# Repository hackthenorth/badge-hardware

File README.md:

# badge-hardware
Physical Hardware Designs for the 2026 Hacker Badge Project

IBOM Link: https://hackathon.github.io/badge-hardware/badge-ibom.html

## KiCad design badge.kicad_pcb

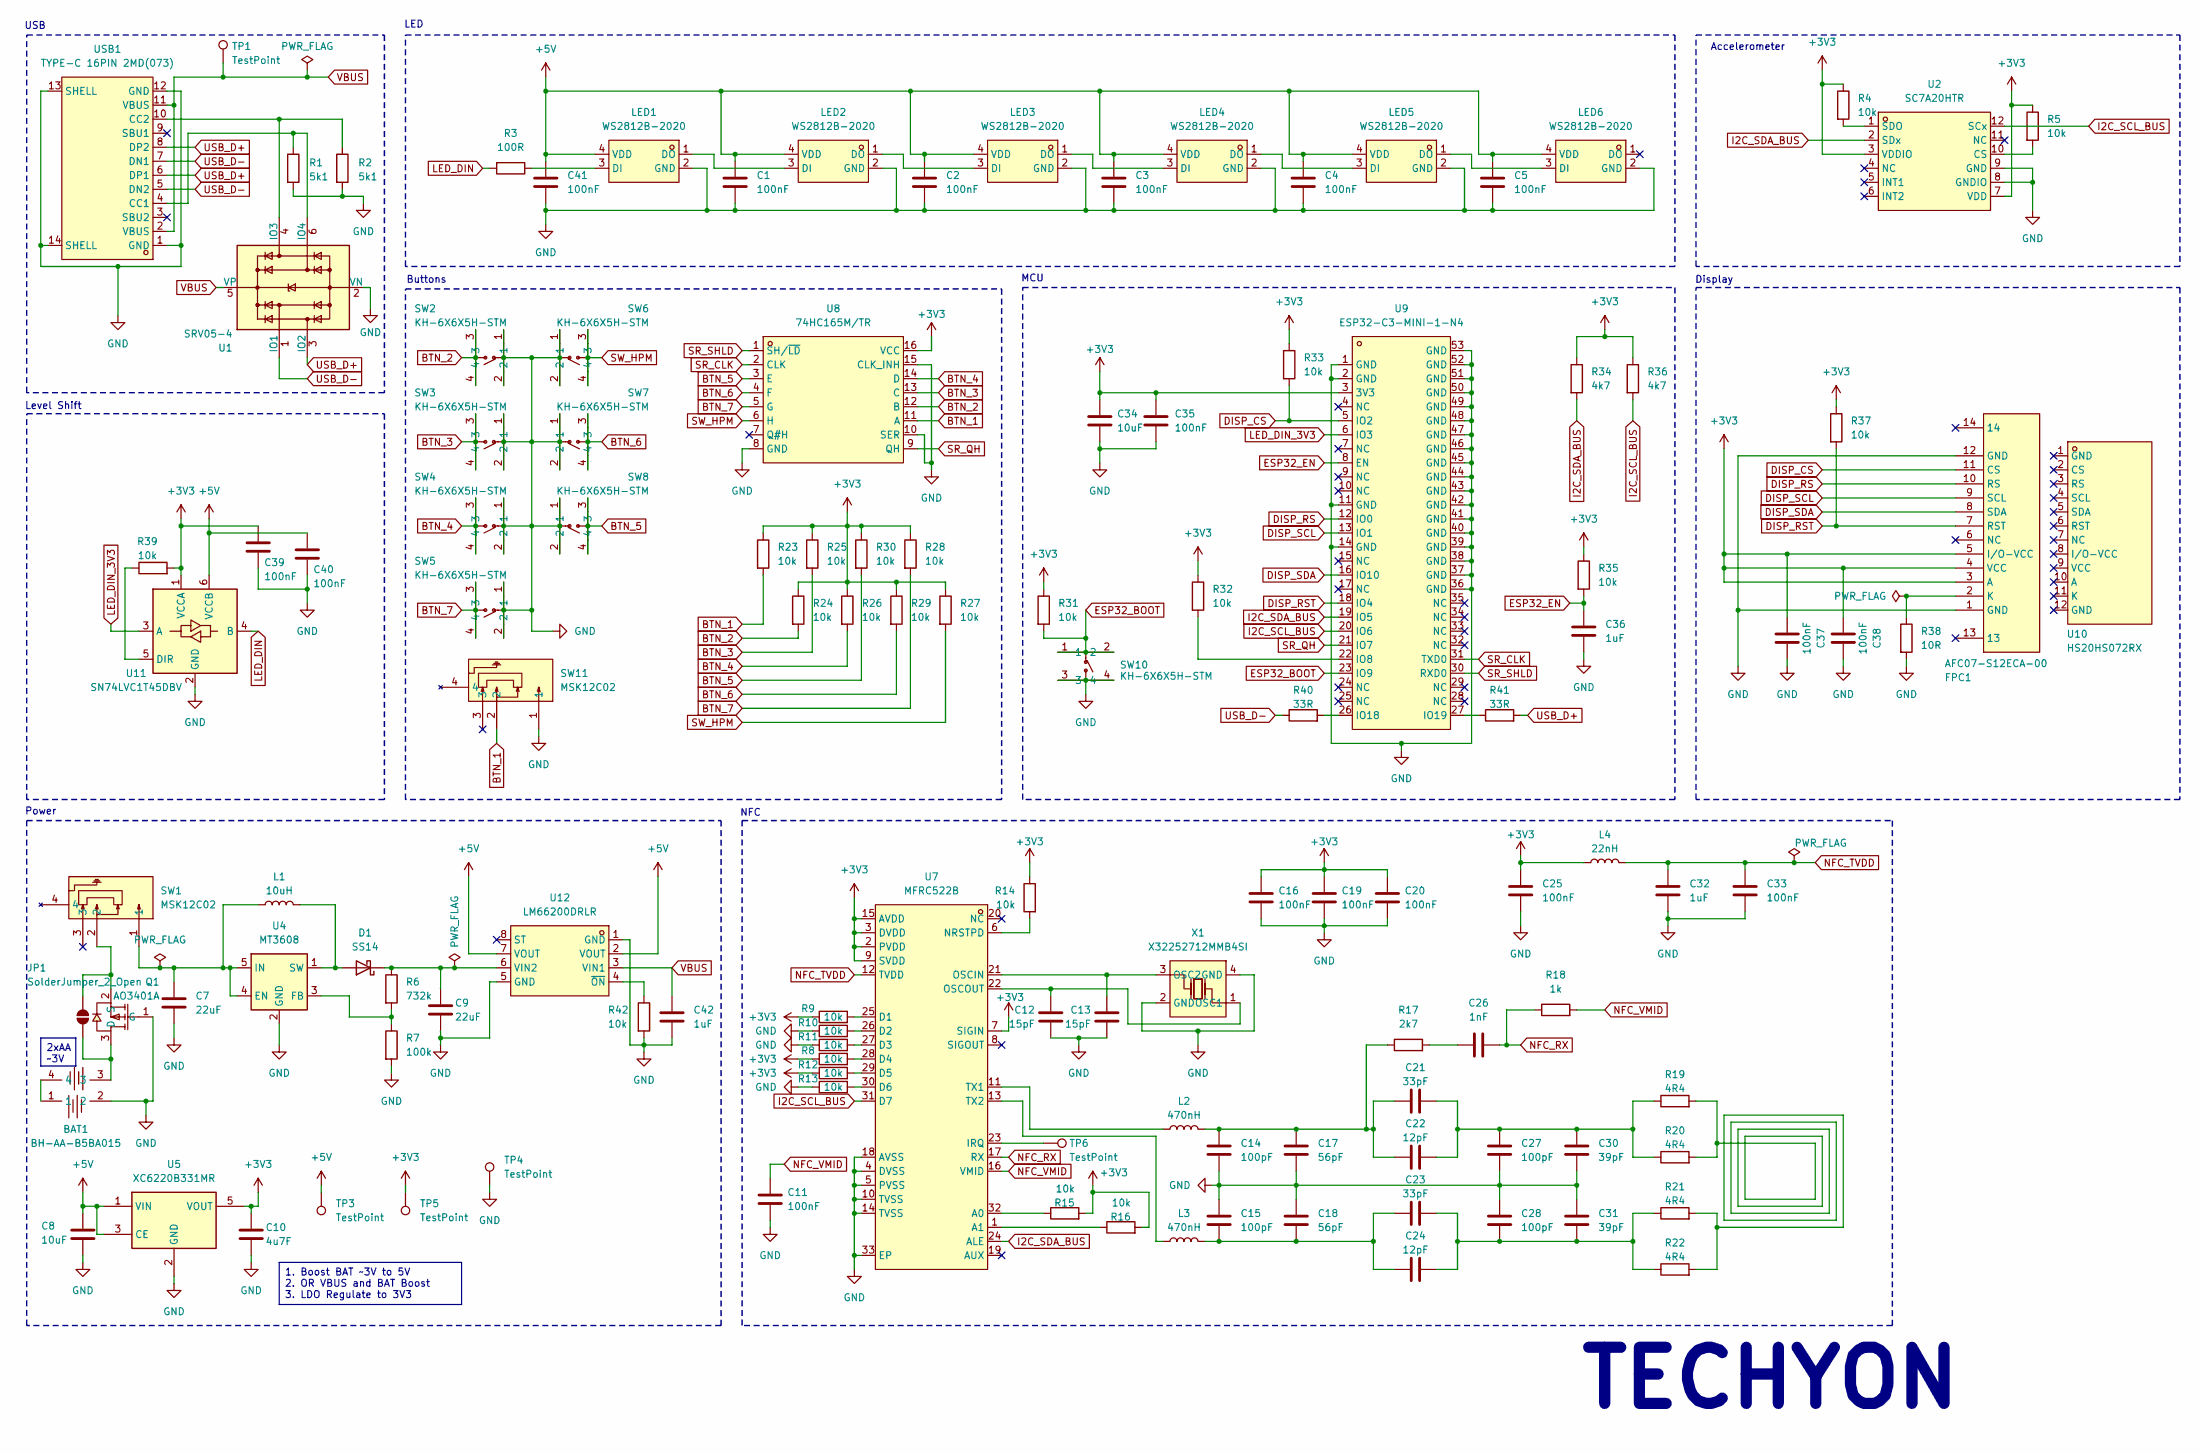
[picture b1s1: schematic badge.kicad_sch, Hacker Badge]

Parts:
BAT1: BH-AA-B5BA015; BAT-SMD_BH-AA-B5BA015; LCSC Part C5290182
C1, C2, C3, C4, C5, C11, C16, C19, C20, C25, C33, C41: 100nF; C_0805_2012Metric
C7, C9: 22uF; C_0805_2012Metric; LCSC Part C45783
C8, C34: 10uF; C_0805_2012Metric; LCSC Part C440198
C10: 4u7F; C_0805_2012Metric; LCSC Part C1779
C12, C13: 15pF; C_0805_2012Metric
C14, C15, C27, C28: 100pF; C_0805_2012Metric
C17, C18: 56pF; C_0805_2012Metric
C21, C23: 33pF; C_0805_2012Metric
C22, C24: 12pF; C_0805_2012Metric
C26: 1nF; C_0805_2012Metric
C30, C31: 39pF; C_0805_2012Metric
C32, C42: 1uF; C_0805_2012Metric
C35, C37, C38, C39, C40: 100nF; C_0805_2012Metric; LCSC Part C49678
C36: 1uF; C_0805_2012Metric; LCSC Part C28323
D1: SS14; D_SMA; LCSC Part C2480
FPC1: AFC07-S12ECA-00; FPC-SMD_12P-P0.50_AFC07-S12ECA-00; LCSC Part C262585
JP1: SolderJumper_2_Open; SolderJumper-2_P1.3mm_Open_Pad1.0x1.5mm
L1: 10uH; L_0805_2012Metric; LCSC Part C440198
L2, L3: 470nH; L_0805_2012Metric
L4: 22nH; L_0805_2012Metric
LED1, LED2, LED3, LED4, LED5, LED6: WS2812B-2020; LED-SMD_4P-L2.0-W2.0-TL_WS2812B-2020; LCSC Part C965555
Q1: AO3401A; SOT-23_L2.9-W1.3-P1.90-LS2.4-BR; MPN AO3401A; LCSC Part C15127
R1, R2: 5k1; R_0805_2012Metric; LCSC Part C27834
R3: 100R; R_0805_2012Metric
R4, R5, R8, R9, R10, R11, R12, R13, R14, R15, R16, R23, R24, R25, R26, R27, R28, R29, R30, R32, R33, R42: 10k; R_0805_2012Metric
R6: 732k; R_0805_2012Metric; LCSC Part C2684593
R7: 100k; R_0805_2012Metric; LCSC Part C149504
R17: 2k7; R_0805_2012Metric
R18: 1k; R_0805_2012Metric
R19, R20, R21, R22: 4R4; R_0805_2012Metric
R31, R35, R37, R39: 10k; R_0805_2012Metric; LCSC Part C17414
R34, R36: 4k7; R_0805_2012Metric
R38: 10R; R_0805_2012Metric; LCSC Part C17415
R40, R41: 33R; R_0805_2012Metric
SW1, SW11: MSK12C02; SW-TH_MSK12C02; LCSC Part C431540
SW2, SW3, SW4, SW5, SW6, SW7, SW8, SW10: KH-6X6X5H-STM; SW-SMD_4P-L6.0-W6.0-P4.50-LS9.0_H5.0; LCSC Part C2837531
TP1, TP3, TP4, TP5, TP6: TestPoint; TestPoint_Pad_D1.5mm
U1: SRV05-4; SOT-23-6; LCSC Part C7420376
U2: SC7A20HTR; LGA-12_L2.0-W2.0-P0.50-TL; LCSC Part C19274408
U4: MT3608; SOT-23-6; LCSC Part C84817
U5: XC6220B331MR; SOT-23-5; LCSC Part C22466451
U7: MFRC522B; VQFN-32_L5.0-W5.0-P0.50-BL-EP3.3; LCSC Part C41361613
U8: 74HC165M/TR; SOP-16_L10.0-W3.9-P1.27-LS6.0-BL; LCSC Part C507184
U9: ESP32-C3-MINI-1-N4; WIFIM-SMD_ESP32-C3-MINI-1; LCSC Part C2838502
U10: HS20HS072RX; OLED-SMD_HS20HS072RX; LCSC Part C5329582
U11: SN74LVC1T45DBV; SOT-23-6; LCSC Part C7843
U12: LM66200DRLR; SOT-583-8_L2.1-W1.2-P0.50-LS1.6-BL; LCSC Part C3235556
USB1: TYPE-C 16PIN 2MD(073); USB-C-SMD_TYPE-C-6PIN-2MD-073; LCSC Part C2765186
X1: X32252712MMB4SI; CRYSTAL-SMD_4P-L3.2-W2.5-BL-1; LCSC Part C29975

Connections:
+3V3: C10.2, C16.1, C19.1, C20.1, C25.1, C34.1, C35.1, C37.2, C38.2, C39.1, FPC1.3 (A), FPC1.4 (VCC), FPC1.5 (I/O-VCC), L4.1, R4.1, R5.1, R8.1, R9.1, R12.1, R14.1, R15.2, R16.2, R23.1, R24.1, R25.1, R26.1, R27.1, R28.1, R29.1, R30.1, R31.1, R32.1, R33.1, R34.1, R35.1, R36.1, R37.1, R39.2, TP5.1, U2.3 (VDDIO), U2.7 (VDD), U5.5 (VOUT), U7.2 (PVDD), U7.3 (DVDD), U7.7 (SIGIN), U7.9 (SVDD), U7.15 (AVDD), U8.16 (VCC), U9.3 (3V3), U11.1 (VCCA)
+5V: C1.1, C2.1, C3.1, C4.1, C5.1, C8.2, C40.1, C41.1, LED1.4 (VDD), LED2.4 (VDD), LED3.4 (VDD), LED4.4 (VDD), LED5.4 (VDD), LED6.4 (VDD), TP3.1, U5.1 (VIN), U5.3 (CE), U11.6 (VCCB), U12.2 (VOUT), U12.7 (VOUT)
BTN_1: R23.2, SW11.2, U8.11 (A)
BTN_2: R24.2, SW2.3, SW2.4, U8.12 (B)
BTN_3: R25.2, SW3.3, SW3.4, U8.13 (C)
BTN_4: R26.2, SW4.3, SW4.4, U8.14 (D)
BTN_5: R30.2, SW8.3, SW8.4, U8.3 (E)
BTN_6: R29.2, SW7.3, SW7.4, U8.4 (F)
BTN_7: R28.2, SW5.3, SW5.4, U8.5 (G)
DISP_CS: FPC1.11 (CS), R33.2, U9.5 (IO2)
DISP_RS: FPC1.10 (RS), U9.12 (IO0)
DISP_RST: FPC1.7 (RST), R37.2, U9.18 (IO4)
DISP_SCL: FPC1.9 (SCL), U9.13 (IO1)
DISP_SDA: FPC1.8 (SDA), U9.16 (IO10)
ESP32_BOOT: R31.2, SW10.1, SW10.2, U9.23 (IO9)
ESP32_EN: C36.1, R35.2, U9.8 (EN)
GND: BAT1.2, C1.2, C2.2, C3.2, C4.2, C5.2, C7.2, C8.1, C9.2, C10.1, C11.2, C12.2, C13.2, C14.2, C15.1, C16.2, C17.2, C18.1, C19.2, C20.2, C25.2, C27.2, C28.1, C30.2, C31.1, C32.2, C33.2, C34.2, C35.2, C36.2, C37.1, C38.1, C39.2, C40.2, C41.2, C42.2, FPC1.1 (GND), FPC1.12 (GND), LED1.2 (GND), LED2.2 (GND), LED3.2 (GND), LED4.2 (GND), LED5.2 (GND), LED6.2 (GND), Q1.1 (G), R1.2, R2.2, R7.2, R10.1, R11.1, R13.1, R38.2, R42.2, SW2.1, SW2.2, SW3.1, SW3.2, SW4.1, SW4.2, SW5.1, SW5.2, SW6.1, SW6.2, SW7.1, SW7.2, SW8.1, SW8.2, SW10.3, SW10.4, SW11.1, TP4.1, U1.2 (VN), U2.8 (GNDIO), U2.9 (GND), U4.2 (GND), U5.2 (GND), U7.4 (DVSS), U7.5 (PVSS), U7.10 (TVSS), U7.14 (TVSS), U7.18 (AVSS), U7.33 (EP), U8.8 (GND), U8.10 (SER), U8.15 (CLK_INH), U9.1 (GND), U9.2 (GND), U9.11 (GND), U9.14 (GND), U9.36 (GND), U9.37 (GND), U9.38 (GND), U9.39 (GND), U9.40 (GND), U9.41 (GND), U9.42 (GND), U9.43 (GND), U9.44 (GND), U9.45 (GND), U9.46 (GND), U9.47 (GND), U9.48 (GND), U9.49 (GND), U9.50 (GND), U9.51 (GND), U9.52 (GND), U9.53 (GND), U11.2 (GND), U12.1 (GND), U12.5 (GND), USB1.1 (GND), USB1.12 (GND), USB1.13 (SHELL), USB1.14 (SHELL), X1.2 (GND), X1.4 (GND)
I2C_SCL_BUS: R36.2, U2.12 (SCx), U7.31 (D7), U9.20 (IO6)
I2C_SDA_BUS: R34.2, U2.2 (SDx), U7.24 (ALE), U9.19 (IO5)
LED_DIN: R3.2, U11.4 (B)
LED_DIN_3V3: U9.6 (IO3), U11.3 (A)
NFC_RX: C26.2, R18.1, U7.17 (RX)
NFC_TVDD: C32.1, C33.1, L4.2, U7.12 (TVDD)
NFC_VMID: C11.1, R18.2, U7.16 (VMID)
unnamed: BAT1.1, BAT1.4
unnamed: C14.1, C17.1, C21.1, C22.1, L2.2, R17.1
unnamed: C15.2, C18.2, C23.1, C24.1, L3.2
unnamed: C21.2, C22.2, C27.1, C30.1, R19.1, R20.1
unnamed: C23.2, C24.2, C28.2, C31.2, R21.1, R22.1
unnamed: C26.1, R17.2
unnamed: D1.2 (A), L1.2, U4.1 (SW)
unnamed: C9.1, D1.1 (K), R6.1, U12.6 (VIN2)
unnamed: FPC1.2 (K), R38.1
unnamed: BAT1.3, JP1.1 (A), Q1.3 (D)
unnamed: JP1.2 (B), Q1.2 (S), SW1.2
unnamed: LED1.3 (DI), R3.1
unnamed: LED1.1 (DO), LED2.3 (DI)
unnamed: LED2.1 (DO), LED3.3 (DI)
unnamed: LED3.1 (DO), LED4.3 (DI)
unnamed: LED4.1 (DO), LED5.3 (DI)
unnamed: LED5.1 (DO), LED6.3 (DI)
unnamed: R19.2, R20.2, R21.2, R22.2
unnamed: R2.1, U1.4 (IO3), USB1.10 (CC2)
unnamed: R1.1, U1.6 (IO4), USB1.4 (CC1)
unnamed: R5.2, U2.10 (CS)
unnamed: R4.2, U2.1 (SDO)
unnamed: C7.1, L1.1, SW1.1, U4.4 (EN), U4.5 (IN)
unnamed: R6.2, R7.1, U4.3 (FB)
unnamed: R15.1, U7.32 (A0)
unnamed: R16.1, U7.1 (A1)
unnamed: R9.2, U7.25 (D1)
unnamed: R10.2, U7.26 (D2)
unnamed: R11.2, U7.27 (D3)
unnamed: R8.2, U7.28 (D4)
unnamed: R12.2, U7.29 (D5)
unnamed: R13.2, U7.30 (D6)
unnamed: TP6.1, U7.23 (IRQ)
unnamed: R14.2, U7.6 (NRSTPD)
unnamed: C13.1, U7.21 (OSCIN), X1.3 (OSC2)
unnamed: C12.1, U7.22 (OSCOUT), X1.1 (OSC1)
unnamed: L2.1, U7.11 (TX1)
unnamed: L3.1, U7.13 (TX2)
unnamed: R32.2, U9.22 (IO8)
unnamed: R40.2, U9.26 (IO18)
unnamed: R41.1, U9.27 (IO19)
unnamed: R39.1, U11.5 (DIR)
unnamed: R42.1, U12.4 (~ON)
SR_CLK: U8.2 (CLK), U9.31 (TXD0)
SR_QH: U8.9 (QH), U9.21 (IO7)
SR_SHLD: U8.1 (SH/~LD), U9.30 (RXD0)
SW_HPM: R27.2, SW6.3, SW6.4, U8.6 (H)
USB_D+: R41.2, U1.3 (IO2), USB1.6 (DP1), USB1.8 (DP2)
USB_D-: R40.1, U1.1 (IO1), USB1.5 (DN2), USB1.7 (DN1)
VBUS: C42.1, TP1.1, U1.5 (VP), U12.3 (VIN1), USB1.2 (VBUS), USB1.11 (VBUS)

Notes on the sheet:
USB
Display
NFC
TECHYON
LED
Power
Buttons
Accelerometer
Level Shift
MCU
2xAA ~3V
1. Boost BAT ~3V to 5V 2. OR VBUS and BAT Boost 3. LDO Regulate to 3V3

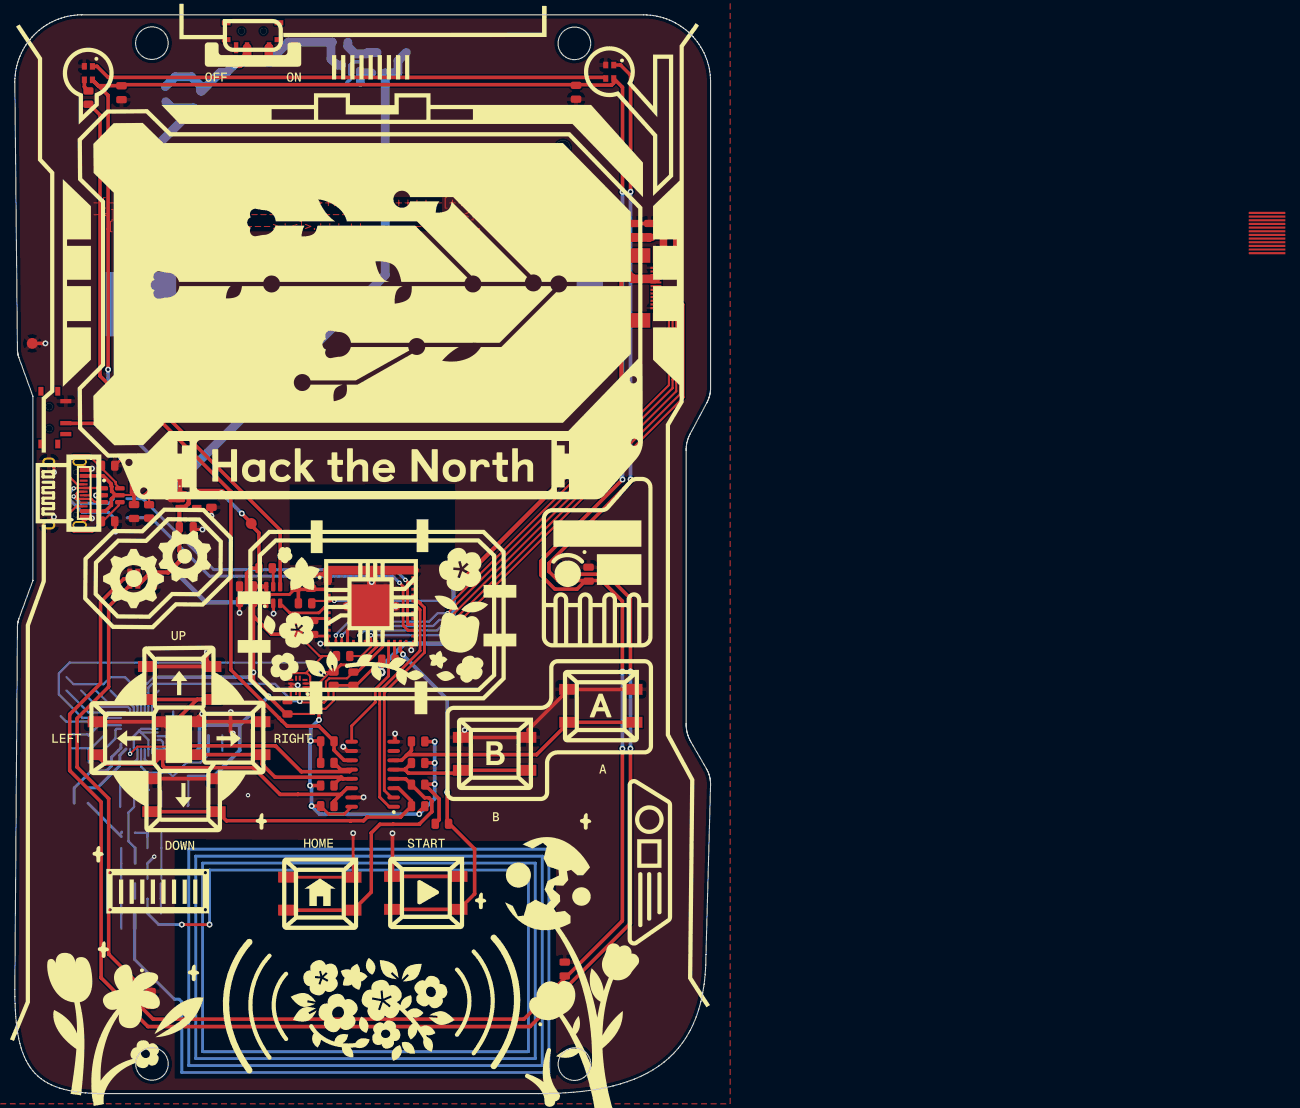
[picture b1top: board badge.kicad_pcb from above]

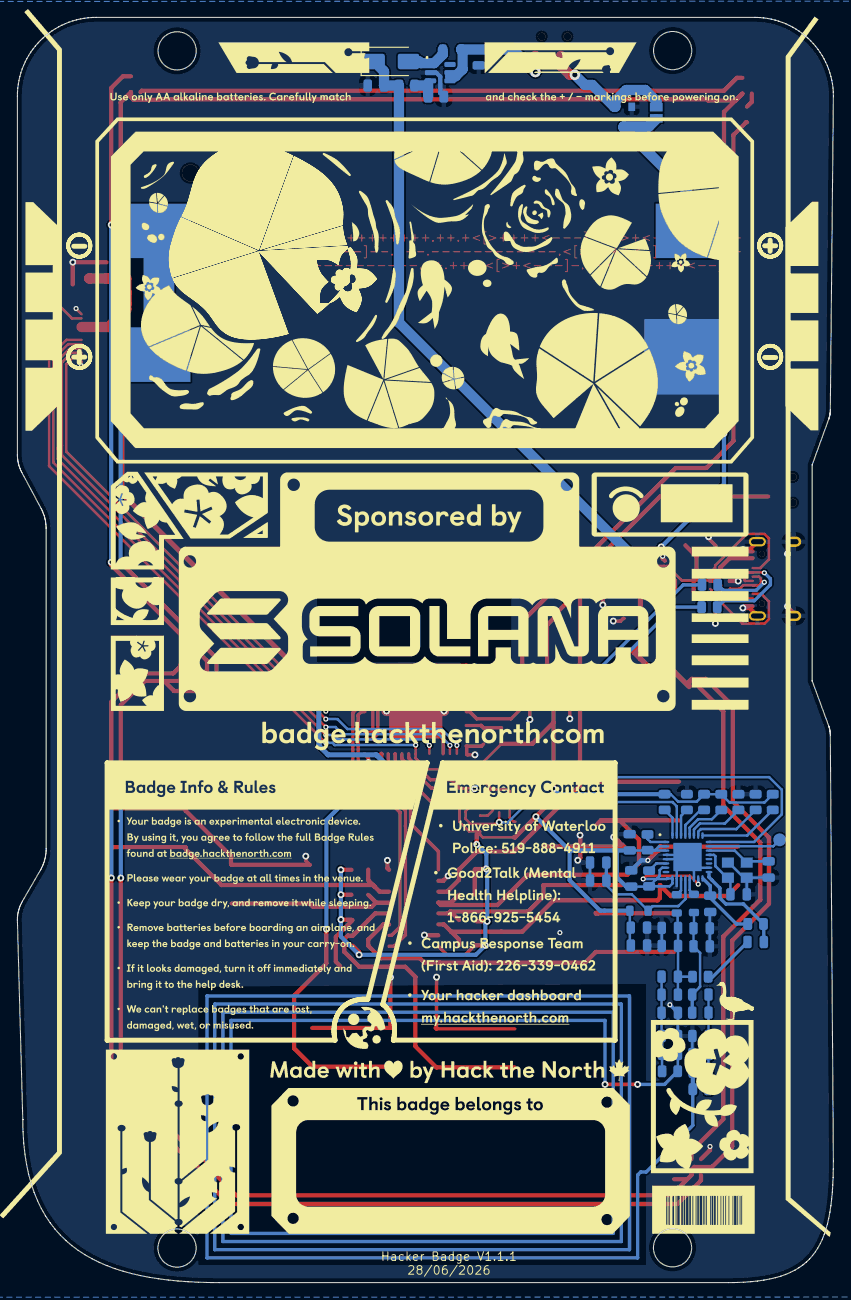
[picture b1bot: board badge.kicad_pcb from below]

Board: 2 copper layers, 95.0 x 147.3 mm, 124 parts (55 on the bottom side), 74 nets.
